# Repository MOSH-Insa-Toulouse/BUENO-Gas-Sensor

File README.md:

# Connected gas sensor

## Author
Théo BUENO, 2018

Part of the gas sensor circuit was designed by Jean-Louis NOULLET.

## About this project
This project is part of the Microcontrollers and Open-Source Hardware (Smart Devices) lecture of the Innovative Smart Systems program at INSA Toulouse.

During this lecture we learned specifics of microcontrollers through Arduino and Open-Source Hardware. We learned how to leverage the Arduino platform to prototype and quickly iterate projects.

We also learned to use the KiCad EDA free software to design our own PCBs.

The evaluation of this class is a (this) project that gave us the opportunity to make use of everything we learned on a practical project: a LoRa-connected gas sensor.

## Presentation
This gas sensor is a standalone Arduino board embedded a RN2483 LoRa modem, a nanoparticle gas sensor with its amplification circuit and a connector for a Grove MQ-x gas sensor (for calibration purposes).

It can be reprogrammed through external headers, and was designed for the lowest power consumption possible.

![alt text][side]

The Atmega328P handles communication over UART with the LoRa modem and connects to the LoRaWAN network "The Things Network".

Data acquisition from the gas sensor can be made with the integrated grove sensor, or with the embedded nanoparticles gas sensor through Atmega328p's DAC.

There are two LEDs: one indicates power supply and the other data transmission over the Atmega328P's hardware serial (for programming). Both are optional. The RN2483 is controlled over software UART. The microcontroller can reset the RN2483 when needed.

## Software
### Atmega328P
#### Bootloader
Brand new Atmega328Ps are not burned with a bootloader that allow for the Arduino IDE to reflash them through serial.

In order to flash them, you need to burn the bootloader included with the Arduino distribution. This process needs any working Arduino board and a virgin Atmega chip. Process can be found on the official Arduino documentation: [Burning the Bootloader](https://www.arduino.cc/en/Tutorial/ArduinoToBreadboard).

#### Firmware
Firmware can be compiled and flashed with the Arduino IDE. You need a USB/Serial adapter like [Sparkfun's FTDI Basic Breakout](https://www.sparkfun.com/products/9716) which has a compatible header pinout with this project.

#### Arduino
Software is a single file Arduino program. Communication and interfacing with the RN2483 modem is done with the [The Things Network Arduino library](https://www.thethingsnetwork.org/docs/devices/arduino/).

We simply poll the ADC to get the value from the gas sensor. If values reaches a threshold data is sent over the LoRaWAN network to the NodeRed dashboard.

We support LoRa downlinks.

LoRa trame counter could use Atmega328P's internal EEPROM. If not, trame count check should be disabled on the LoRa network used (The Things Network dashboard for instance). I chose not to because EEPROMs have a limited write cycle count.

### Dashboard
To handle uplinks received over The Things Network, one may use a Node-RED server with the official [TTN Node-RED package](https://github.com/TheThingsNetwork/nodered-app-node).

The [quickstart](https://github.com/TheThingsNetwork/nodered-app-node/blob/master/docs/quickstart.md) page guides through the set-up of such system. You can then handle your data with any Node-RED connected system.

I successfully set-up a dashboard which logs received messages from the sensor in a console.

## Hardware
All hardware components were designed using the KiCad EDA. KiCad is free software and developed by volunteers all around the world. You can support its continued development by [donating to the CERN Foundation](https://giving.web.cern.ch/civicrm/contribute/transact?reset=1&id=6), which is investing a lot of ressources and efforts to make KiCad a competitive software.

### Schematic
The schematic was designed using hierarchical sheets.
![alt text][schematic]

You can navigate to and from any submodules by using the hierarchy view tool on KiCad. This way you can also see the connections between submodules of the design in a clear way. The drawback of this method is that it generates prints with lots of pages even for small circuits.

### Circuit design
![alt text][PCB]
The circuit is 1-layer only (top), with the 2nd layer (bottom) being the ground plane. Only one connection could not be routed on the top side and required two vias to put a strap on the top (the 3.3V line between regulator and RN2483 modem).

![alt text][bottom]

I tried to minimize as much as possible the PCB footprint, and I do not think it could get much smaller with the amount of THT components and the RN2483 breakout we use.

Track size is 20 mil, with 24 mil isolation.

### Power
The embedded gas sensor needs to be regenerated by heating up its internal resistor. This process is very power hungry and can be triggered only when needed by the microcontroller by piloting a MOSFET. This prevents sensor heating from uselessly draining power from supply.

Power supply can be provided by a male jack connector, or with the male headers on the board. Power source is selected with the switch located just behind the jack connector. If one of the power source is not connected, switch acts as a power on/off control.

On the Grove gas sensor that can be used for calibration, there is no control over heating, hence if it is connected it will drain power for as long as it is connected (about 400 mAH in experiments).

LoRa modem RN2483 uses about 20 to 30 mAH when transmitting, and 3.3V power supply is provided by a dedicated regulator. A voltage divider with resistors was also tested and proved to work but drained battery even when the modem was idle.

The Atmega328P should not take more than 20 mAH, which make this circuit quite power efficient when not transmitting or recycling sensor.

You have the option to "hack" the board to use a voltage divider with two resistors in lieu of the 3.3V regulator thanks to its compatible pin layout.

### Improvements
Big TO-220 packages are a waste of space. Design would benefit from smaller packages for 3.3V/5V regulators and MOSFET.

There is no logic level shifter between the RN2483 (3.3V logic) and the Atmega328P (5V logic). Pray that your RN2483 is 5V tolerant .

Some tracks are really close to the mounting holes of the RN2483 breakout or to pads. It would be better to optimize routing and components placement to isolate them better.

We could imagine a design with an onboard battery charger coupled with photovoltaic cells and a battery, that could allow for sensor recycling when a lot of power is available. That would make this sensor completely power self-dependant. Presently extended use is not possible on batteries, although its power management makes it quite power efficient (40 mAH at 5V is 0.2W).

[top]: Images/top.png "Board preview from the top"
[side]: Images/top_side.png "Board preview from the side"
[bottom]: Images/bottom.png "Board preview from the bottom"
[PCB]: Images/PCB.png "PCB preview"
[schematic]: Images/schematic_main.png "Main sheet schematic view"

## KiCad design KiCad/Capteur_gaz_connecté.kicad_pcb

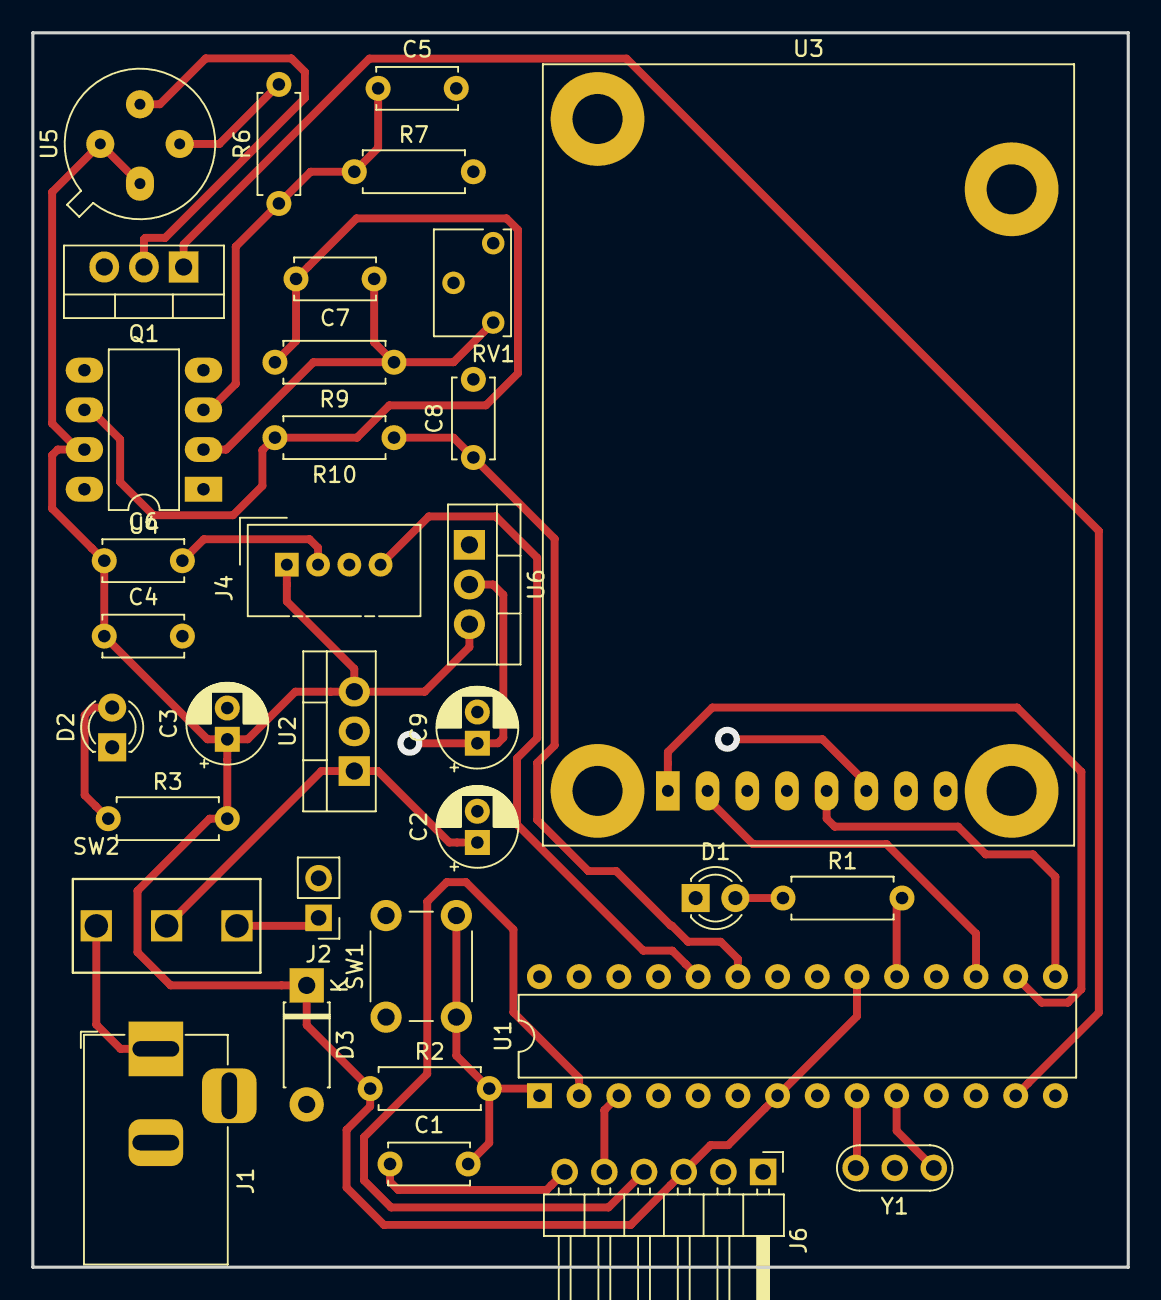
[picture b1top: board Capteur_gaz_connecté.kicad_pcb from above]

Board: 2 copper layers, 70.1 x 79.0 mm, 34 parts (0 on the bottom side), 26 nets.

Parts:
C1, C4: 0,1µ; C_Disc_D5.0mm_W2.5mm_P5.00mm
C2, C3, C9: 47µ; CP_Radial_D5.0mm_P2.00mm
C5, C6, C8: 100n; C_Disc_D5.0mm_W2.5mm_P5.00mm
C7: 1µ; C_Disc_D5.0mm_W2.5mm_P5.00mm
D1, D2: LED; LED_D3.0mm
D3: D; D_DO-41_SOD81_P7.62mm_Horizontal
J1: Barrel_Jack_MountingPin; BarrelJack_Horizontal
J2: Conn_01x02_Male; PinHeader_1x02_P2.54mm_Vertical
J4: conn_groove_gas_sensor; NS-Tech_Grove_1x04_P2mm_Vertical
J6: Conn_01x06_Male; PinHeader_1x06_P2.54mm_Horizontal
Q1: IRF740; TO-220-3_Vertical
R1, R3: 330; R_Axial_DIN0207_L6.3mm_D2.5mm_P7.62mm_Horizontal
R2, R6: 10k; R_Axial_DIN0207_L6.3mm_D2.5mm_P7.62mm_Horizontal
R7, R9: 100k; R_Axial_DIN0207_L6.3mm_D2.5mm_P7.62mm_Horizontal
R10: 1k; R_Axial_DIN0207_L6.3mm_D2.5mm_P7.62mm_Horizontal
RV1: abt 10k; Potentiometer_Vishay_T73XX_Horizontal
SW1: SW_Push; SW_PUSH_6mm
SW2: SW_DPDT_x2; Switch_SPDT_THT_6x12
U1: ATmega328P-PU; DIP-28_W7.62mm
U2: LM7805_TO220; TO-220-3_Vertical
U3: RN2483; RN2483_Breakout
U4: LTC1050; DIP-8_W7.62mm_LongPads
U5: AIME
U6: TLV1117-33; TO-220-3_Vertical
Y1: Crystal_GND2; Resonator-3Pin_W7.0mm_H2.5mm

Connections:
/MCU/mcu_pwr_5v: C3.1, C4.1, C6.1, D3.1, J4.1, J6.3, R2.1, R3.2, U1.7, U1.20, U2.3, U4.7, U5.1, U5.4, U6.3
/MCU/mcu_radio_rst: U1.15, U3.5
/MCU/mcu_radio_rx: U1.16, U3.1
/MCU/mcu_radio_tx: U1.17, U3.2
/MCU/mcu_rst: C1.1, J6.6
/MCU/mcu_rx: J6.4, U1.2
/MCU/mcu_tx: J6.5, U1.3
/Power/pwr_3v3: C9.1, U3.6, U6.2
/Sensors/aime_gas_heating: Q1.1, U1.13
/Sensors/aime_gas_sig: C8.1, R10.1, U1.23
/Sensors/groove_gas_sig: J4.4, U1.24
/Sensors/heat_aime: Q1.2, U5.3
GND: C2.2, C3.2, C4.2, C5.2, C6.2, C8.2, C9.2, D1.1, D2.1, D3.2, J1.2, J2.2, J4.2, J6.1, Q1.3, R7.2, RV1.3, SW1.1, U1.8, U1.22, U2.2, U3.8, U4.4, U6.1, Y1.2
unnamed: C1.2, R2.2, SW1.2, U1.1
unnamed: C2.1, SW2.2, U2.1
unnamed: C5.1, R6.1, R7.1, U4.3
unnamed: C7.1, R9.1, RV1.1, U4.2
unnamed: C7.2, R9.2, R10.2, U4.6
unnamed: D1.2, R1.1
unnamed: D2.2, R3.1
unnamed: J1.1, SW2.1
unnamed: J2.1, SW2.3
unnamed: R1.2, U1.19
unnamed: R6.2, U5.2
unnamed: U1.9, Y1.3
unnamed: U1.10, Y1.1

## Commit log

2018-11-27 initial hardware release
2018-11-30 add software, readme updates
2018-11-30 add info about Node-RED
